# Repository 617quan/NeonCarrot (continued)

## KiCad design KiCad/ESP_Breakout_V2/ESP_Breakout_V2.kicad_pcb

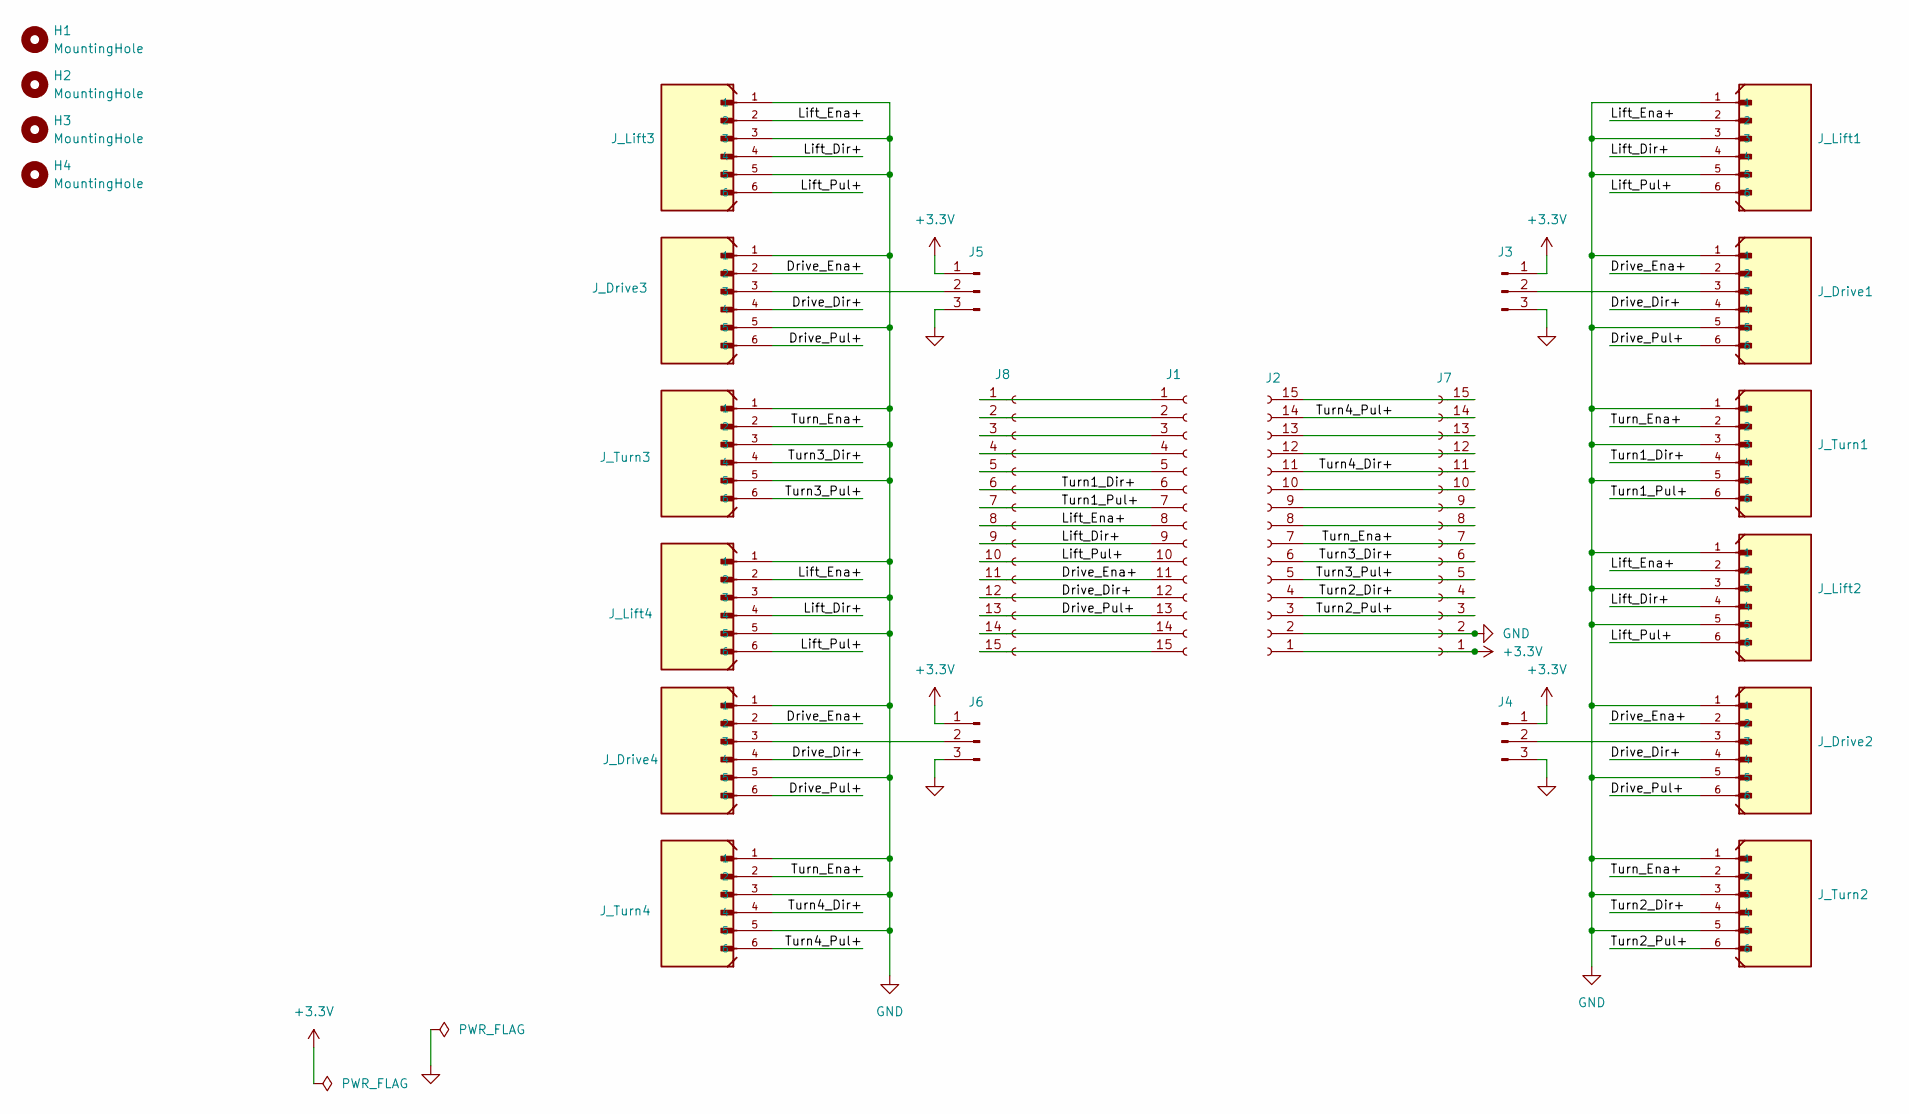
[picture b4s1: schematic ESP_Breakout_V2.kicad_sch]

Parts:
H1, H2, H3, H4: MountingHole; MountingHole_3.2mm_M3
J1, J2, J7, J8: Conn_01x15_Socket; PinSocket_1x15_P2.54mm_Vertical
J3, J4, J5, J6: Conn_01x03_Pin; PinHeader_1x03_P2.54mm_Vertical
J_Drive1, J_Drive2, J_Drive3, J_Drive4: B6B-PH-K-S; JST_PH_B6B-PH-K_1x06_P2.00mm_Vertical
J_Lift1, J_Lift2, J_Lift3, J_Lift4: B6B-PH-K-S; JST_PH_B6B-PH-K_1x06_P2.00mm_Vertical
J_Turn1, J_Turn2, J_Turn3, J_Turn4: B6B-PH-K-S; JST_PH_B6B-PH-K_1x06_P2.00mm_Vertical

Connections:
+3.3V: J2.1, J3.1, J4.1, J5.1, J6.1, J7.1
/Drive_Dir+: J1.12, J8.12, J_Drive1.4, J_Drive2.4, J_Drive3.4, J_Drive4.4
/Drive_Ena+: J1.11, J8.11, J_Drive1.2, J_Drive2.2, J_Drive3.2, J_Drive4.2
/Drive_Pul+: J1.13, J8.13, J_Drive1.6, J_Drive2.6, J_Drive3.6, J_Drive4.6
/Lift_Dir+: J1.9, J8.9, J_Lift1.4, J_Lift2.4, J_Lift3.4, J_Lift4.4
/Lift_Ena+: J1.8, J8.8, J_Lift1.2, J_Lift2.2, J_Lift3.2, J_Lift4.2
/Lift_Pul+: J1.10, J8.10, J_Lift1.6, J_Lift2.6, J_Lift3.6, J_Lift4.6
/Turn1_Dir+: J1.6, J8.6, J_Turn1.4
/Turn1_Pul+: J1.7, J8.7, J_Turn1.6
/Turn2_Dir+: J2.4, J7.4, J_Turn2.4
/Turn2_Pul+: J2.3, J7.3, J_Turn2.6
/Turn3_Dir+: J2.6, J7.6, J_Turn3.4
/Turn3_Pul+: J2.5, J7.5, J_Turn3.6
/Turn4_Dir+: J2.11, J7.11, J_Turn4.4
/Turn4_Pul+: J2.14, J7.14, J_Turn4.6
/Turn_Ena+: J2.7, J7.7, J_Turn1.2, J_Turn2.2, J_Turn3.2, J_Turn4.2
GND: J2.2, J3.3, J4.3, J5.3, J6.3, J7.2, J_Drive1.1, J_Drive1.5, J_Drive2.1, J_Drive2.5, J_Drive3.1, J_Drive3.5, J_Drive4.1, J_Drive4.5, J_Lift1.1, J_Lift1.3, J_Lift1.5, J_Lift2.1, J_Lift2.3, J_Lift2.5, J_Lift3.1, J_Lift3.3, J_Lift3.5, J_Lift4.1, J_Lift4.3, J_Lift4.5, J_Turn1.1, J_Turn1.3, J_Turn1.5, J_Turn2.1, J_Turn2.3, J_Turn2.5, J_Turn3.1, J_Turn3.3, J_Turn3.5, J_Turn4.1, J_Turn4.3, J_Turn4.5
unnamed: J1.1, J8.1
unnamed: J1.2, J8.2
unnamed: J1.3, J8.3
unnamed: J1.4, J8.4
unnamed: J1.5, J8.5
unnamed: J1.14, J8.14
unnamed: J1.15, J8.15
unnamed: J2.8, J7.8
unnamed: J2.9, J7.9
unnamed: J2.10, J7.10
unnamed: J2.12, J7.12
unnamed: J2.13, J7.13
unnamed: J2.15, J7.15
unnamed: J3.2, J_Drive1.3
unnamed: J4.2, J_Drive2.3
unnamed: J5.2, J_Drive3.3
unnamed: J6.2, J_Drive4.3

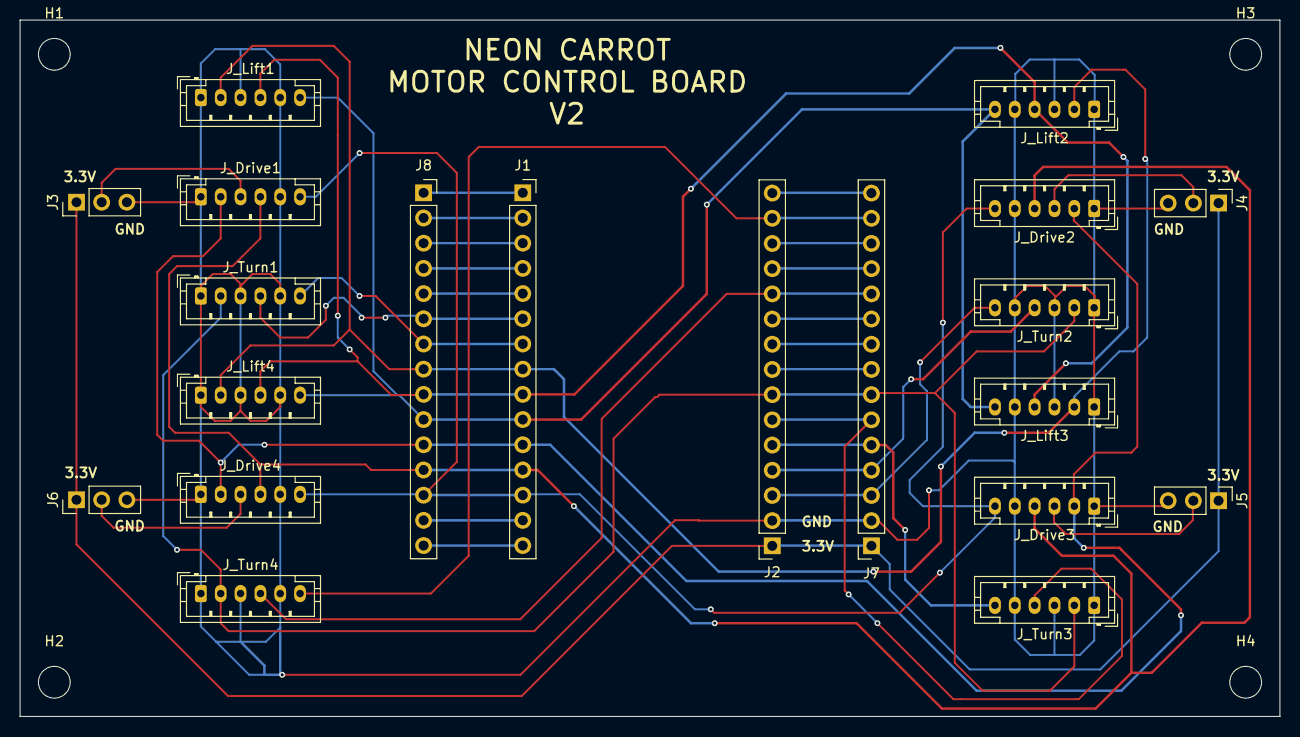
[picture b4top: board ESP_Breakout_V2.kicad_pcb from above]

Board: 2 copper layers, 127.0 x 70.2 mm, 24 parts (0 on the bottom side), 34 nets.

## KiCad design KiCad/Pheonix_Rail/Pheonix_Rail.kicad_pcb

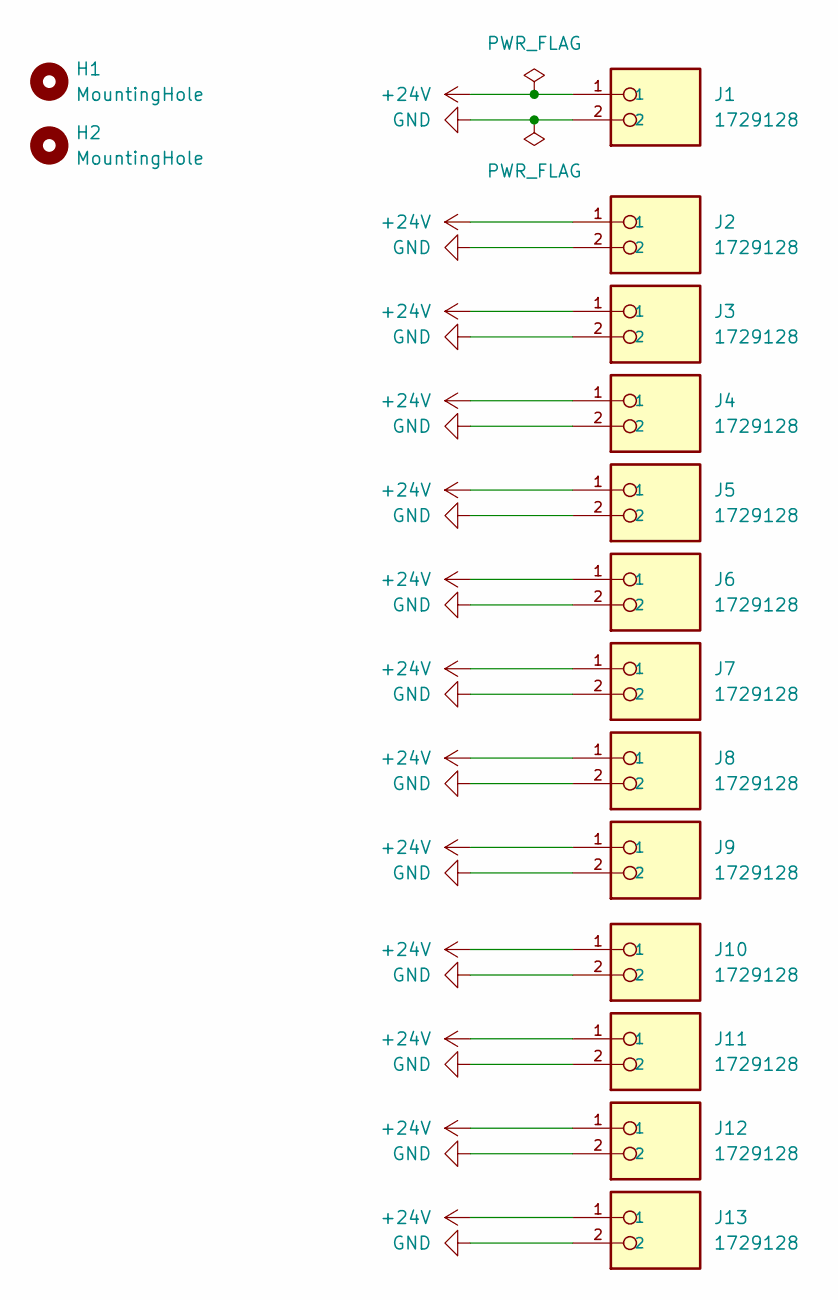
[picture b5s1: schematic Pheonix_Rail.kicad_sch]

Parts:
H1, H2: MountingHole; MountingHole_2.5mm
J1, J2, J3, J4, J5, J6, J7, J8, J9, J10, J11, J12, J13: 1729128; PHOENIX_1729128; PARTREV 28.07.2023

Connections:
+24V: J1.1, J2.1, J3.1, J4.1, J5.1, J6.1, J7.1, J8.1, J9.1, J10.1, J11.1, J12.1, J13.1
GND: J1.2, J2.2, J3.2, J4.2, J5.2, J6.2, J7.2, J8.2, J9.2, J10.2, J11.2, J12.2, J13.2

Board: 2 copper layers, 15 parts (0 on the bottom side), 2 nets, no tracks yet.

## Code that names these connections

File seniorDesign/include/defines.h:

/********** defines.h **********
 *
 * Created by Team Neon Carrot. Contact Carrot Griffin Faecher for Info
 * Provides all global constants, enumerations, and hardware configuration
 * values used throughout the robot control software. This file centralizes
 * definitions for system states, movement commands, motor control messages,
 * pin assignments, and mechanical conversion constants.
 *
 * The header also contains parameters used to translate real world movement
 * (inches or degrees) into stepper motor microsteps based on gearbox ratios,
 * wheel geometry, and microstepping configuration. Motor speed and
 * acceleration limits are also defined here so they can be tuned in a single
 * location without modifying motor control code.
 *
 ****************************************/

#ifndef _DEFINES
#define _DEFINES

/* STATE MACHINE TYPES */

typedef enum {
    P1,
    P2,
    P3,
    P4,
    MOVING
} STATE_TYPE;

typedef enum {
    MOVE_TO_P1,
    MOVE_TO_P2,
    MOVE_TO_P3,
    MOVE_TO_P4,
    IDLE,
    INITIALIZE
} MOVE_COMMAND;

/* DECLARED SO THAT ODD MESSAGES GO TO ESP1, AND EVEN MESSAGES GO TO ESP2 */
typedef enum {
    END_STAGE = 0,

    /* ESP1 COMMANDS (odd) */
    WHEELS_UP            = 1,
    WHEELS_DOWN          = WHEELS_UP + 2,
    MOVE_FORWARDS_24_IN  = WHEELS_DOWN + 2,
    MOVE_BACKWARDS_24_IN = MOVE_FORWARDS_24_IN + 2,
    TURN_RIGHT_90_DEGREES= MOVE_BACKWARDS_24_IN + 2,
    TURN_LEFT_90_DEGREES = TURN_RIGHT_90_DEGREES + 2,
    TURN_RIGHT_45_DEGREES= TURN_LEFT_90_DEGREES + 2,
    TURN_LEFT_45_DEGREES = TURN_RIGHT_45_DEGREES + 2,
    TURN_RIGHT_135_DEGREES= TURN_LEFT_45_DEGREES + 2,
    TURN_LEFT_135_DEGREES = TURN_RIGHT_135_DEGREES + 2,
    INIT_LIFT = TURN_LEFT_135_DEGREES + 2,

    /* ESP2 COMMANDS (even) */
    INITIATE_TURN_MOTORS = 2,
    RETURN_TURN_MOTORS   = INITIATE_TURN_MOTORS + 2,
    INIT_TURN = RETURN_TURN_MOTORS + 2,

    FINISH_MOVEMENT = 100

} MOTOR_COMMAND;

/* ESP1 PINOUT */

#define DRIVE_ENABLE 13

#define FRONT_DRIVE_DIRECTION 12
#define FRONT_DRIVE_PULSE 14

#define BACK_DRIVE_DIRECTION 27
#define BACK_DRIVE_PULSE 26

#define LIFT_ENABLE 18 
#define LIFT_DIRECTION 23

#define LIFT1_PULSE 19 
#define LIFT2_PULSE 21 
#define LIFT3_PULSE 2 
#define LIFT4_PULSE 15 

/* LIMIT SWITCHES */

#define BOARD1_LIMIT1 22
#define BOARD1_LIMIT2 25
#define BOARD1_LIMIT3 32
#define BOARD1_LIMIT4 33

#define BOARD2_LIMIT1 19
#define BOARD2_LIMIT2 22
#define BOARD2_LIMIT3 5
#define BOARD2_LIMIT4 21

/* ESP2 PINOUT */

#define TURN_ENABLE 13

#define TURN1_PULSE 14 
#define TURN1_DIRECTION 12 

#define TURN2_PULSE 33 
#define TURN2_DIRECTION 25 

#define TURN3_PULSE 32 
#define TURN3_DIRECTION 23

#define TURN4_PULSE 26 
#define TURN4_DIRECTION 27 

/* UART Pin Defines. RXD2 and TXD2 are the specified pins on the board, while
RXD1 and TXD1 are both remapped for UART channel 1 */
#define TXD1 5
#define RXD1 18
#define TXD2 17
#define RXD2 16

/* DEFINES FOR CONVERTING REAL LIFE DISTANCES TO STEPS FOR THE MOTORS */
#define WHEEL_DIAMETER 5.9035
#define WHEEL_CIRCUMFERENCE (PI * WHEEL_DIAMETER)
#define DRIVE_GEARBOX_RATIO 30
#define TURN_GEARBOX_RATIO 100
#define MICROSTEP 8
#define FULL_DRIVE_ROTATION (MICROSTEP * 200 * DRIVE_GEARBOX_RATIO)
#define FULL_TURN_ROTATION (MICROSTEP * 200 * TURN_GEARBOX_RATIO)
#define STEPS_PER_LIFT_HUNDREDTH_INCH 28846 /* NOTE: EXPERIMENTALLY FOUND */

/* THESE ARE THE ONLY AMOUNTS THE TURN MOTORS WILL EVER NEED TO TURN */

#define TURN_1_3_NUM_STEPS ((45.0f / 360.0f) * (float)FULL_TURN_ROTATION) // 20,000
#define TURN_2_4_NUM_STEPS ((148.0f / 360.0f) * (float)FULL_TURN_ROTATION) // 60,000

#define IN_FOR_45_DEGREE_TURN 11.35
#define IN_FOR_90_DEGREE_TURN 22.7
#define IN_FOR_135_DEGREE_TURN 33.95

/* SPEED AND ACCELERATION DEFINES FOR ALL MOTOR TYPES. NOTE: INCREASING THESE
VALUES MAY CAUSE MOTORS TO STALL */

#define TURN_2_4_MAX_SPEED 11250
#define TURN_1_3_MAX_SPEED (TURN_2_4_MAX_SPEED / 3)

#define TURN_2_4_ACCEL 3375
#define TURN_1_3_ACCEL (TURN_2_4_ACCEL / 3)

#define TURN_INIT_SPEED TURN_1_3_MAX_SPEED

#define DRIVE_MAX_SPEED 5000
#define DRIVE_ACCEL 2000

#define LIFT_MAX_SPEED 27000 
#define LIFT_ACCEL 1500

#endif

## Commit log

2025-09-25 Added Bonnie's Code
2025-10-01 FastAccelStepper library
2025-10-03 Create initialCode
2025-10-08 seniorDesignCode
2025-10-08 Start fresh COMMIT TO MAIN ONLY KEEP BONNIES CODE
2025-10-08 Made a New PlatformIO Project
2025-10-08 10/07/25 Progress
    added wheel.cpp
    added wheel.h (motor struct)
    worked on main.cpp
    pinout_defines.h to define pinout
2025-10-08 connected pins to struct
    Put motor struct in wheel class
    connected pins to drive motor
2025-10-08 Using the ledc functions to make a square wave
2025-10-08 Square wave finally oscillates, just really slow and clunky
2025-10-08 weird folders in bonnie code
2025-10-09 motor.cpp and motor.h created, and a shit ton of documentation on StepperEngine
2025-10-09 motor constructor constructed
2025-10-10 We got a bouncing wave zaddies
2025-10-10 How do I make this make a full rotation?
2025-10-15 Bye bye motor class hello wheel class
2025-10-24 Added struct to wheel.h for pins, wheel initialization is a little different, and movement functions are updated with new functionality
2025-10-28 It isn't working, but I'm trying to fix it
2025-10-28 shit doesn't work
2025-10-29 Done for the day. Main is a mess but the class works
2025-10-30 started spi
2025-10-30 Skeleton for SPI in main.cpp
    haven't tested but need to make another main with child code, this code is for the parent esp
2025-10-30 SPI rework
    Changed master slave lingo to computer peripheral MOSI -> COPI. Finished the parent main.cpp didn't figure out child main.cpp also didn't build
2025-10-31 i didn't achieve anything
2025-10-31 Added SPI child implementation
    Haven't debugged yet but parent esp is using arduino <SPI.h>, child is using ESP-IDF functions.
2025-11-03 mid debug for SPI
    sorry not finished. Also having UART open would solve all of the issues in 1/10 the time
2025-11-05 child fucntion not working
    only because we are lazy. rec_buf has the correct message from parent we just don't know how to translate it to a something to return.
2025-11-05 Updated child main should work
    Not tested but should work
2025-11-11 State Machine
    Bare bones state machine. Need to edit child and parent SPI mains to transmit ints and not char arrays to interface with state machine (will make sending messages easier SLAY and faster SLAY)
2025-11-12 parent and child spi transmitting uint8_t messages
    lez plug this in and see if it works
2025-11-12 i forgo the state machine
2025-11-12 Sending int commands
2025-11-13 About to start writing new motor class
2025-11-16 Frame class compiles. Just copied from wheel
2025-11-17 Documentation for frame struct done
2025-11-17 Made frame_board_main.cpp to flash frame code. It's a spi child
2025-11-19 after Tuesday night
2025-11-21 Everything before design review
2025-11-21 webServer Addition
    pushing webServer
2025-11-21 adding KiCad project to repo
2025-11-22 Interfaced web server class w/ frame class
2026-01-23 Adding kicad stuff
2026-01-24 Worked on schematic
2026-01-25 import esp32 devkit
2026-01-25 saved changes
2026-01-27 footprint assignments
2026-01-27 push
2026-01-28 starting pcb layout
2026-01-30 wiring progress
2026-02-02 start of pheonix
2026-02-03 starting turning
2026-02-03 Adding my changes
2026-02-03 hehehe
2026-02-03 worked on layout
2026-02-03 Some minor cleanup of frame.h
2026-02-03 changed mounting holes
2026-02-05 layout for phoenix board
2026-02-05 Updated some library stuff
2026-02-05 State machine logic skeleton
2026-02-06 Made Gerbers
2026-02-06 friday work
2026-02-06 fixed lift motor max speed
2026-02-12 Finished Rough Layout!
2026-02-12 Fixed some via stuff
2026-02-16 monday work
2026-02-16 Add conversion shit and editing state machine
2026-02-17 esp32 custom board
    erm not done yet
2026-02-17 emergency stawwwwppppp
2026-02-17 Bare metal update
    Added VSPI connector and other stuff
2026-02-18 about to test arduino mega
2026-02-18 blah
2026-02-19 after working on wednesday
2026-02-19 MotorGroup Compiles
2026-02-19 MotorGroup should function correctly
2026-02-21 Variable delay function
2026-02-25 driver board updating
2026-02-26 Kicad stuff
2026-02-26 Work after Wednesday
2026-02-27 Some cleanup of motorGroup, and defines
2026-02-27 Crazy upgrade to webserver that wont work
2026-02-27 Changing the state machine
    This is absolute hell
2026-02-27 Did some initial routing on breakout2
2026-02-28 Cleaned up routing
2026-02-28 Added Ground Plane and stiching vias
2026-03-02 Needs some more work on 2esp
2026-03-03 The 4 positions
2026-03-03 possible improvements to the website
2026-03-04 Final KiCad stuff for 2ESP and Driver Board
2026-03-05 datasheets for BOM
2026-03-05 non blocking movement done along with web server improvements
2026-03-05 Documented everything and removed old unused code
2026-03-05 state machine is right now
2026-03-08 Started the big board
2026-03-10 Limit switch software ongoing
    Started adding framework for limit switch implementation for initialization for lift motors.
2026-03-10 delete
2026-03-10 add bomboclat button
2026-03-27 Forgot to push a lot
2026-03-30 Limit switches pt 1
2026-03-31 Turn motors initialize (needs fine tuning)
2026-04-07 works, but more fine tuning is needed
2026-04-23 doesnt work
2026-04-28 Code for Working Demo
2026-05-02 Adding Cad files
2026-05-02 more CAD files added
